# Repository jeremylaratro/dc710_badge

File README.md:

# DC710 Badge — DEF CON 34 (B-2 Spirit)

Flying-wing PCB badge in a real B-2 Spirit silhouette.  ESP32-C3 +
SA868-V VHF transceiver, single-cell LiPo, USB-C charging, OLED display,
4× WS2812 RGB LEDs, 3× tactile buttons, SAO header.

**Board:** 200 × 77 mm (≈ 7.87" tip-to-tip), real B-2 proportions
(wingspan/length ≈ 2.5).  Outline extracted from a real B-2 STL mesh —
3 aft-pointing spikes, engine-cutout notches, sharp swept wingtips.

### 3D render — Top (F.Cu)

### 3D render — Bottom (B.Cu)

### Official blueprint — Front

### Official blueprint — Back

---

## What's in the project

### Hardware
- **MCU:** ESP32-C3-MINI-1 module (official Espressif footprint, 53 pads)
- **Radio:** G-NiceRF SA868-V VHF (134–174 MHz) walkie-talkie module
- **Display:** SSD1306 0.96" OLED, 7-pin SPI
- **Power:** USB-C → SS14 Schottky → TP4056 LiPo charger → AP2112K-3.3 LDO
- **Battery:** Single-cell LiPo via JST-PH 2-pin
- **UI:** 4× WS2812B-2020 RGB LEDs, 3× TL3342 tactile (RESET / SEL / UP / DN), green status LED
- **Expansion:** SAO v1.69bis 2x3 header, 1×4 debug UART header

---

## ESP32-C3 GPIO map

| GPIO | Pad | Function |
|---|---|---|
| EN  |  6 | Reset (S1 + R4 + C7 RC) |
| 0   | 13 | WS2812 LED chain DIN (R11 220Ω series) |
| 1   | 14 | OLED DC |
| 2   |  7 | SA868 audio RX (ADC1_CH2, mid-rail biased) |
| 3   |  8 | UP button |
| 4   | 27 | SA868 PTT |
| 5   | 28 | OLED CS |
| 6   | 30 | OLED SCK |
| 7   | 31 | OLED MOSI |
| 8   | 20 | DOWN button (strap, pull-up at boot) |
| 9   | 19 | SEL / BOOT (strap, pull-up) |
| 10  | 11 | SA868 UART TX (UART1) |
| 18  | 16 | USB D− |
| 19  | 17 | USB D+ |
| 20  | 23 | SA868 UART RX |
| 21  | 24 | OLED RES |

---

## What's left to hand-finish

- [x] Route the 3 remaining nets in pcbnew (audio LPF cluster).
- [x] Move 4 short traces out of the antenna keep-out zones (RF perf).
- [x] Reposition silkscreen reference designators that overlap pads.
- [ ] Complete firmware development
- [ ] Complete hardware CTF
- [ ] Order Gerbers 

---

## Potential Obstacles

1. **PCB trace antenna performance at VHF will be poor.**  ~150 mm of
   meander on a flying-wing PCB at 145 MHz is electrically short — expect
   single-digit-negative dBi gain.  Fine for in-room foxhunt; not for DX.
   The match network has DNP shunts (C50 / C51) for VNA tuning.
2. **SA868 footprint is hand-built from the NiceRF datasheet.** 
3. **Audio TX synthesis uses `ledcWriteTone()`.**  Adequate for CW /
   beacon tones, not arbitrary audio.

---

## Previous edition

The DEF CON 33 design (smaller 100 × 55 mm board, 3-triangle outline,
hand-rolled symbols) lives in [`defcon33/`](defcon33/).

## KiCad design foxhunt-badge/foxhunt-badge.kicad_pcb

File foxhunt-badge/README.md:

# Foxhunt Badge — DEFCON B-2 Edition

ESP32-C3 + SA868-V VHF transceiver in a B-2 Spirit silhouette PCB.
~$16 BOM at qty 100, single-cell LiPo, **200×80mm** flying-wing form
factor (~7.87" tip-to-tip, real B-2 proportions: wingspan/length ≈ 2.5,
~31° leading-edge sweep).

> **Status (2026-04-25, v1.2): KiCad 9 schematic ERC-clean (0 errors,
> 0 warnings).  PCB on 200×80 mm B-2 outline (4 aft-pointing apexes + 3
> forward notches including center notch).  All 56 footprints inside the
> outline.  U2 uses the **official Espressif ESP32-C3-MINI-1 footprint**
> (53 pads, fetched from github.com/espressif/kicad-libraries).  The
> netlist pin numbers match the official datasheet pinout exactly.
> Freerouting v2.1.0 routed **119 of 131 nets (350 track segments)** in
> a 30-pass autoroute.  12 nets remain unrouted in the dense central
> module area; these need hand-finishing in pcbnew.**

---

## Project layout

```
foxhunt-badge/
├── foxhunt-badge.kicad_pro      # KiCad 9 project file
├── foxhunt-badge.kicad_sch      # schematic (ERC-clean)
├── foxhunt-badge.kicad_pcb      # PCB (placed, ground-poured, awaiting routing)
├── sym-lib-table                # registers project symbol library
├── fp-lib-table                 # registers project footprint library
├── lib/
│   ├── foxhunt.kicad_sym        # custom symbols (ESP32-C3-MINI-1, SA868,
│   │                            #                 TP4056_Module, OLED_SSD1306)
│   └── foxhunt.pretty/          # custom footprints
├── docs/                        # netlist + placement reference
├── fab/
│   ├── lib_gen.py               # regenerate lib/foxhunt.kicad_sym
│   ├── footprint_gen.py         # regenerate lib/foxhunt.pretty/
│   ├── sch_gen.py               # regenerate the schematic
│   ├── pcb_gen.py               # regenerate the PCB
│   ├── generate_b2_outline.py   # parametric B-2 outline generator
│   └── output/                  # Gerbers, drill, BOM, position files
└── firmware/                    # PlatformIO ESP-IDF firmware
```

## What's in the schematic (59 components, 43 nets)

* **Power tree:** USB-C 16P → SS14 Schottky → TP4056 LiPo charger → AP2112K-3.3
  LDO → 3.3 V rail.  3 PWR_FLAG drivers (VBUS, VBAT_RAW, GND) keep ERC happy.
* **MCU:** ESP32-C3-MINI-1 with EN reset RC, 10 µF / 1 µF / 100 nF decoupling,
  RESET / SEL / UP / DN tactiles, USB-C as native USB 2.0 (CDC) plus UART debug
  pass-through (J3).
* **Radio:** SA868-V (VHF) module with PTT / PD pull-ups, UART1 control, audio
  TX low-pass network (R-C-R-C-C), audio RX bias network (DC-block + mid-rail
  divider), trace-antenna match (L1 + DNP shunt caps for VNA tuning).
* **UI:** SSD1306 SPI 0.96" OLED, four WS2812B-2020 RGB LEDs in a chain along
  the leading edge, status LED, 2×3 SAO header, 1×4 debug header.

## ESP32-C3 pin map

| GPIO | Function          |
|------|-------------------|
| 0    | WS2812 DIN        |
| 1    | OLED_DC           |
| 2    | SA868_AUDIO (ADC) |
| 3    | BTN_UP            |
| 4    | SA868_PTT         |
| 5    | OLED_CS           |
| 6    | OLED_SCK          |
| 7    | OLED_MOSI         |
| 8    | BTN_DN            |
| 9    | BTN_SEL (boot)    |
| 10   | SA868_TX (UART1)  |
| 18   | USB_DM            |
| 19   | USB_DP            |
| 20   | SA868_RX (UART1)  |
| 21   | OLED_RST          |

## What still needs hand-finishing

The auto-generated PCB has all footprints positioned and nets assigned, but
the following still need attention in the KiCad GUI:

1. **Routing.** 132 ratsnest connections remain.  Suggested order:
   1. VBUS / VBAT / +3V3 power tree (use 0.5 mm tracks, Power netclass).
   2. RF chain U3.ANT → L1 → trace antenna (Right wingtip, RF netclass).
   3. Audio paths (MIC / RX_OUT) — keep away from WS2812 DIN.
   4. WS2812 daisy-chain along the leading edge.
   5. OLED SPI bus (group SCK/MOSI together).
   6. Buttons, debug header, SAO.
2. **Placement refinement.** ~10 components have minor courtyard overlaps
   from the auto-placer; spread them slightly in the GUI.
3. **Silkscreen.** Reference designators may need to be moved off pads
   (silk-on-copper warnings).
4. **Final DRC pass** before plotting fab outputs.

## Regenerating the project from scratch

```bash
# Library
python3 fab/lib_gen.py
python3 fab/footprint_gen.py

# Schematic + PCB
python3 fab/sch_gen.py
python3 fab/pcb_gen.py

# Validation
kicad-cli sch erc -o /tmp/erc.rpt foxhunt-badge.kicad_sch   # 0 violations
kicad-cli pcb drc -o /tmp/drc.rpt foxhunt-badge.kicad_pcb   # 132 unconnected (ratsnest)

# Fab outputs (after routing in GUI)
mkdir -p fab/output
kicad-cli pcb export gerbers --output fab/output/ foxhunt-badge.kicad_pcb
kicad-cli pcb export drill   --output fab/output/ foxhunt-badge.kicad_pcb
kicad-cli pcb export pos     --output fab/output/foxhunt-badge-pos.csv \
                             --format csv --units mm foxhunt-badge.kicad_pcb
kicad-cli sch export bom     --output fab/output/foxhunt-badge-bom.csv \
                             --fields "Reference,Value,Footprint,MPN,LCSC" \
                             --group-by Value foxhunt-badge.kicad_sch
```

## Custom libraries

Because KiCad's stock libraries don't ship the exact parts we use, four
custom symbols and four custom footprints live in `lib/`:

| Item                          | Symbol | Footprint | Source                             |
|-------------------------------|--------|-----------|------------------------------------|
| ESP32-C3-MINI-1 (53-pad MSMD) | ✓      | ✓         | Espressif datasheet rev 1.1        |
| SA868-V (16-pin castellated)  | ✓      | ✓         | NiceRF SA868 datasheet             |
| TP4056_Module (5-pin breakout)| ✓      | ✓         | LCSC C16581 module                 |
| OLED_SSD1306 7-pin SPI        | ✓      | ✓         | Generic 0.96" OLED breakout        |

These are registered via `sym-lib-table` and `fp-lib-table` and pinned in
the project preferences so they show up first in the picker.

## Firmware build & flash

```bash
cd firmware
pio run                  # build
pio run -t upload        # flash via USB-C
pio device monitor       # serial console at 115200
```

First boot: rainbow chase LEDs, splash OLED, idle animation.
SEL button cycles modes (IDLE → FOX → HUNTER → IDLE).

**Frequency configuration**: `main.cpp` defaults to 146.520 MHz (US 2m
simplex).  Transmitting on this freq requires a US Technician ham license.
For license-free testing, use a SA868-U (UHF) on PMR446 with a shorter
antenna meander.

## Honest disclosures

1. **PCB trace antenna performance at VHF will be poor.**  ~150 mm of meander
   on a 100 mm board at 145 MHz is electrically short — single-digit-negative
   dBi gain expected.  Fine for in-room foxhunt; not for DX.  The match
   network has DNP shunts (C50 / C51) for VNA tuning.  Next rev: add a u.FL
   footprint for an external whip.
2. **SA868 footprint is hand-built from the datasheet.**  Verify the pad
   geometry against your actual modules before fab.
3. **Audio TX synthesis uses ledcWriteTone().**  Adequate for CW/beacon tones,
   not arbitrary audio.  Voice TX would need an external I²S DAC.
4. **Routing is hand-finishing work.**  This generator places components and
   wires nets in the schematic; track routing is left to the GUI (or to a
   freerouting/specctra round-trip).  The placement plan in `docs/` is the
   intended ground truth for layout.

## Next-rev wishlist

* u.FL connector + external VHF whip
* PAM8302 + 8 Ω speaker for RX audio
* ESP32-S3 for more flash / GPIO / color OLED
* Full SAO v1.69bis compliance (needs 4 free GPIOs — likely requires an I/O
  expander on this rev's pin budget)

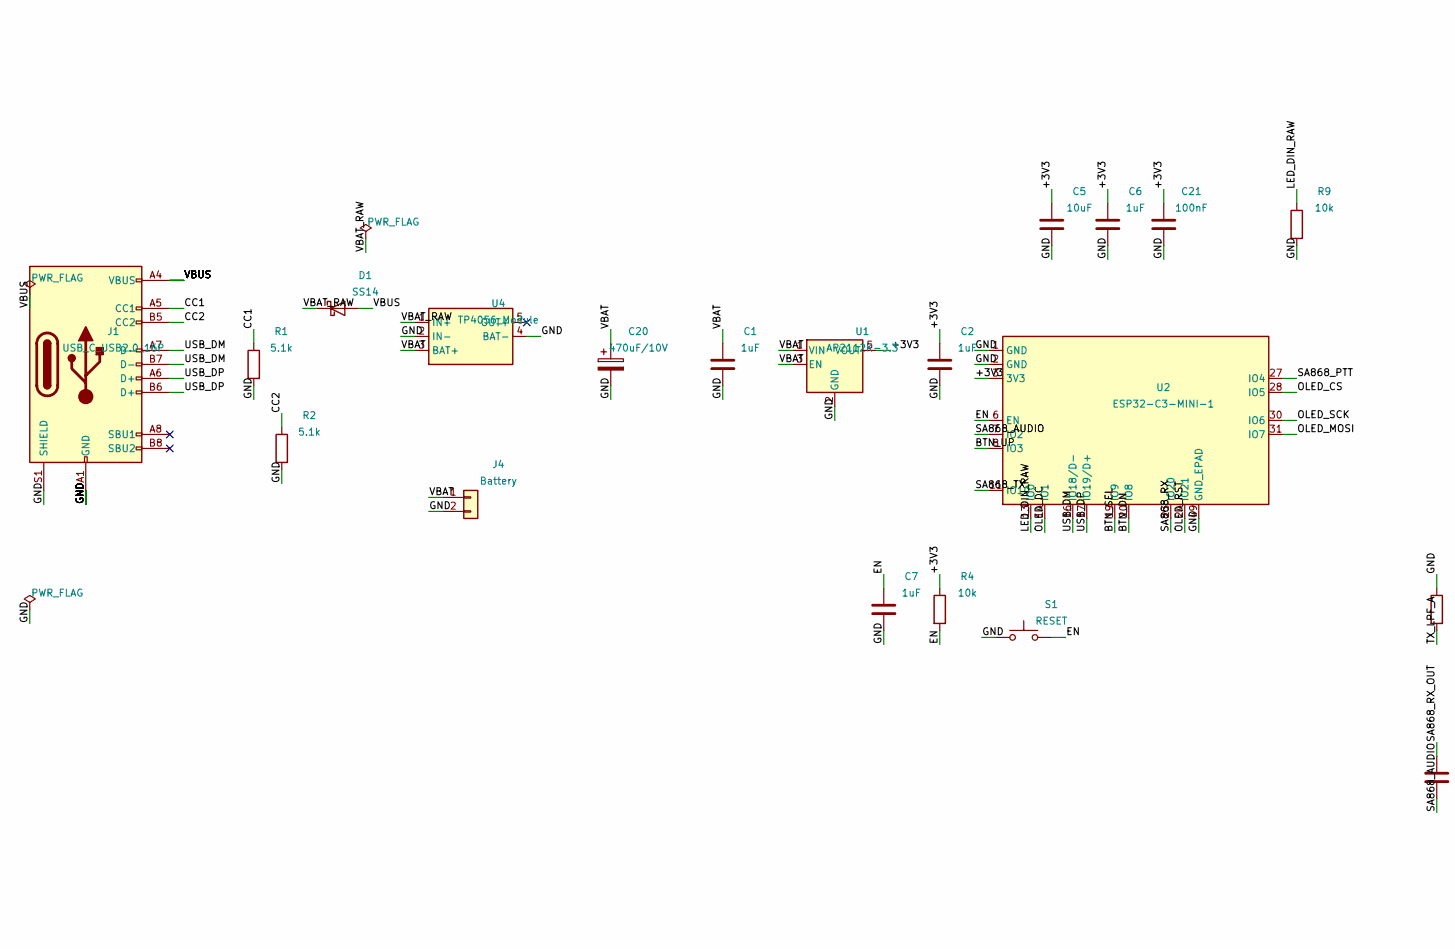
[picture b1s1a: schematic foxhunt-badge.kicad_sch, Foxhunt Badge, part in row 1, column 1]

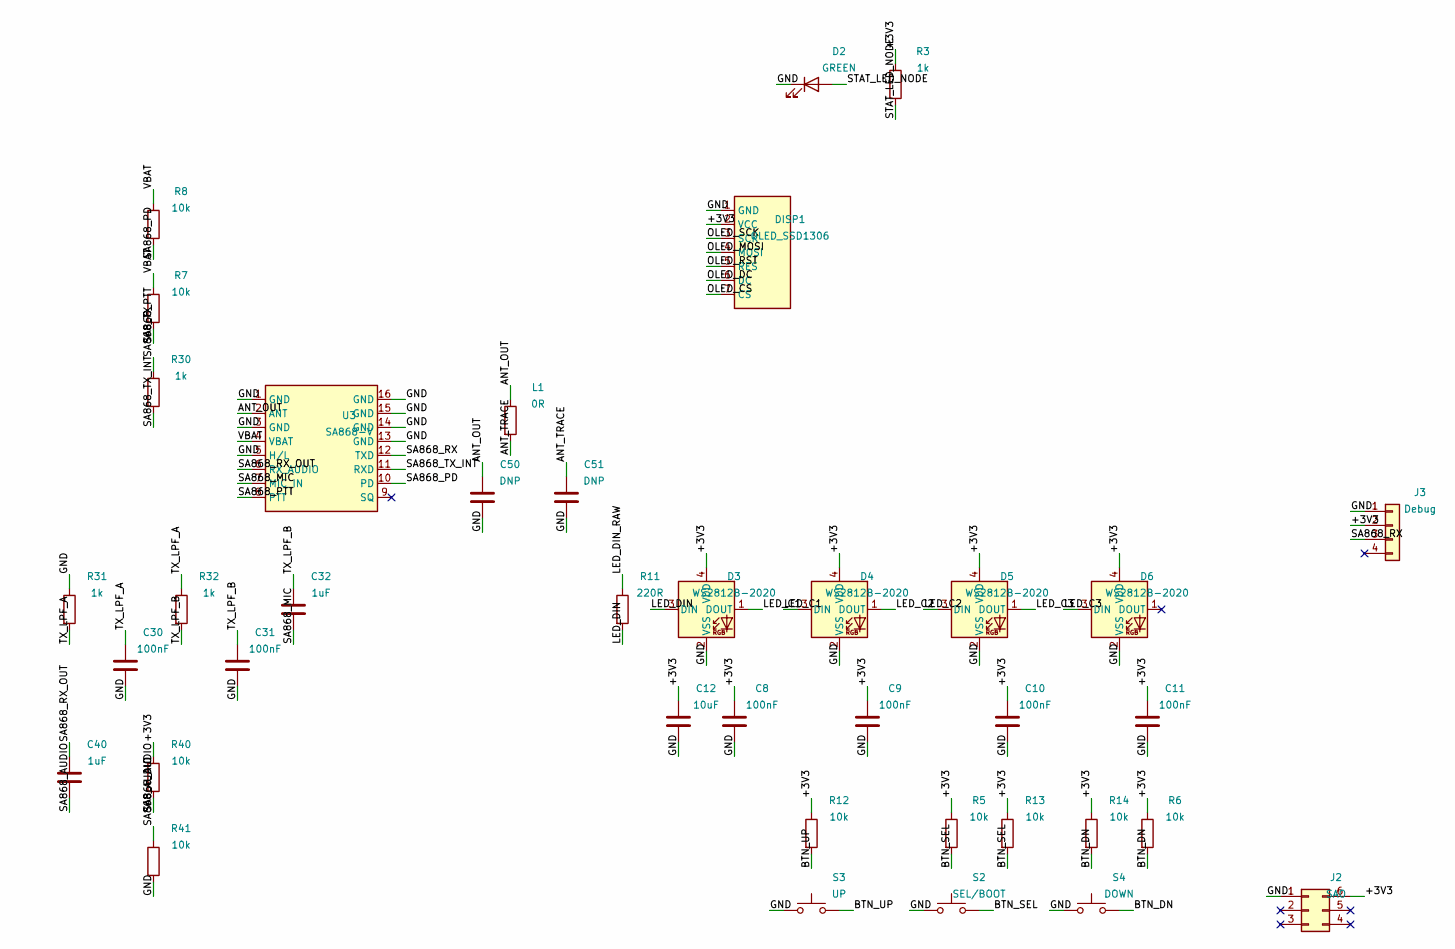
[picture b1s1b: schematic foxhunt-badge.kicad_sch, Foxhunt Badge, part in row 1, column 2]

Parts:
C1, C2, C6, C7, C32, C40: 1uF; C_0603_1608Metric
C5, C12: 10uF; C_0603_1608Metric
C8, C9, C10, C11, C21, C30, C31: 100nF; C_0603_1608Metric
C20: 470uF/10V; CP_Elec_8x10
C50, C51: DNP; C_0603_1608Metric
D1: SS14; D_SOD-123
D2: GREEN; LED_0603_1608Metric
D3, D4, D5, D6: WS2812B-2020; LED_WS2812B-2020_PLCC4_2.0x2.0mm
DISP1: OLED_SSD1306; OLED_SSD1306_128x64_7P
J1: USB_C_USB2.0_16P; USB_C_Receptacle_HRO_TYPE-C-31-M-12
J2: SAO; PinHeader_2x03_P2.54mm_Vertical
J3: Debug; PinHeader_1x04_P2.54mm_Vertical
J4: Battery; JST_PH_S2B-PH-K_1x02_P2.00mm_Horizontal
L1: 0R; R_0603_1608Metric
R1, R2: 5.1k; R_0603_1608Metric
R3, R30, R31, R32: 1k; R_0603_1608Metric
R4, R5, R6, R7, R8, R9, R12, R13, R14, R40, R41: 10k; R_0603_1608Metric
R11: 220R; R_0603_1608Metric
S1: RESET; SW_SPST_TL3342
S2: SEL/BOOT; SW_SPST_TL3342
S3: UP; SW_SPST_TL3342
S4: DOWN; SW_SPST_TL3342
U1: AP2112K-3.3; SOT-23-5
U2: ESP32-C3-MINI-1
U3: SA868-V; SA868
U4: TP4056_Module

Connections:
+3V3: C2.1, C5.1, C6.1, C8.1, C9.1, C10.1, C11.1, C12.1, C21.1, D3.4 (VDD), D4.4 (VDD), D5.4 (VDD), D6.4 (VDD), DISP1.2 (VCC), J2.6, J3.2, R3.1, R4.1, R5.1, R6.1, R12.1, R13.1, R14.1, R40.1, U1.5 (VOUT), U2.3 (3V3)
ANT_OUT: C50.1, L1.1, U3.2 (ANT)
ANT_TRACE: C51.1, L1.2
BTN_DN: R6.2, R14.2, S4.2, U2.20 (IO8)
BTN_SEL: R5.2, R13.2, S2.2, U2.19 (IO9)
BTN_UP: R12.2, S3.2, U2.8 (IO3)
CC1: J1.A5 (CC1), R1.1
CC2: J1.B5 (CC2), R2.1
EN: C7.1, R4.2, S1.2, U2.6 (EN)
GND: C1.2, C2.2, C5.2, C6.2, C7.2, C8.2, C9.2, C10.2, C11.2, C12.2, C20.2, C21.2, C30.2, C31.2, C50.2, C51.2, D2.1 (K), D3.2 (VSS), D4.2 (VSS), D5.2 (VSS), D6.2 (VSS), DISP1.1 (GND), J1.A1 (GND), J1.A12 (GND), J1.B1 (GND), J1.B12 (GND), J1.S1 (SHIELD), J2.1, J3.1, J3.4, J4.2, R1.2, R2.2, R9.2, R31.1, R41.2, S1.1, S2.1, S3.1, S4.1, U1.2 (GND), U2.1 (GND), U2.2 (GND), U2.49 (GND_EPAD), U3.1 (GND), U3.3 (GND), U3.5 (H/L), U3.13 (GND), U3.14 (GND), U3.15 (GND), U3.16 (GND), U4.2 (IN-), U4.4 (BAT-)
LED_C1: D3.1 (DOUT), D4.3 (DIN)
LED_C2: D4.1 (DOUT), D5.3 (DIN)
LED_C3: D5.1 (DOUT), D6.3 (DIN)
LED_DIN: D3.3 (DIN), R11.2
LED_DIN_RAW: R9.1, R11.1, U2.13 (IO0)
LED_END: D6.1 (DOUT)
OLED_CS: DISP1.7 (CS), U2.28 (IO5)
OLED_DC: DISP1.6 (DC), U2.14 (IO1)
OLED_MOSI: DISP1.4 (MOSI), U2.31 (IO7)
OLED_RST: DISP1.5 (RES), U2.24 (IO21)
OLED_SCK: DISP1.3 (SCK), U2.30 (IO6)
SA868_AUDIO: C40.2, R40.2, R41.1, U2.7 (IO2)
SA868_MIC: C32.2, U3.7 (MIC_IN)
SA868_PD: R8.2, U3.10 (PD)
SA868_PTT: R7.2, U2.27 (IO4), U3.8 (PTT)
SA868_RX: J3.3, U2.23 (IO20), U3.12 (TXD)
SA868_RX_OUT: C40.1, U3.6 (RX_AUDIO)
SA868_SQ: U3.9 (SQ)
SA868_TX: R30.1, U2.11 (IO10)
SA868_TX_INT: R30.2, U3.11 (RXD)
SAO_GPIO1: J2.3
SAO_GPIO2: J2.2
SAO_GPIO3: J2.5
SAO_GPIO4: J2.4
STAT_LED_NODE: D2.2 (A), R3.2
TX_LPF_A: C30.1, R31.2, R32.1
TX_LPF_B: C31.1, C32.1, R32.2
USB_DM: J1.A7 (D-), J1.B7 (D-), U2.16 (IO18/D-)
USB_DP: J1.A6 (D+), J1.B6 (D+), U2.17 (IO19/D+)
USB_OUT: U4.5 (OUT+)
VBAT: C1.1, C20.1, J4.1, R7.1, R8.1, U1.1 (VIN), U1.3 (EN), U3.4 (VBAT), U4.3 (BAT+)
VBAT_RAW: D1.1 (K), U4.1 (IN+)
VBUS: D1.2 (A), J1.A4 (VBUS), J1.A9 (VBUS), J1.B4 (VBUS), J1.B9 (VBUS)

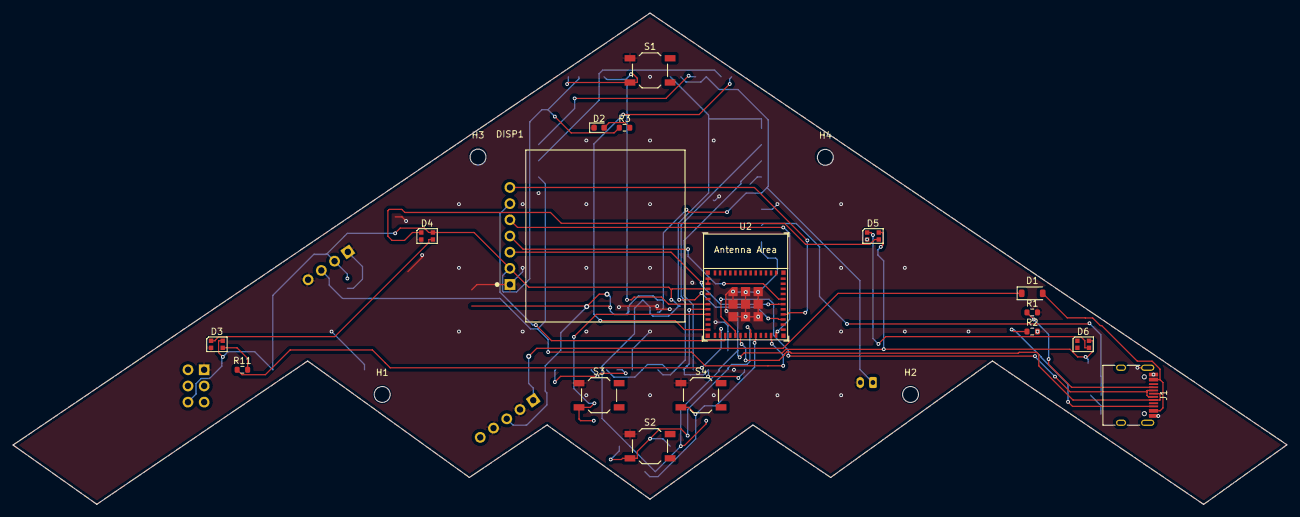
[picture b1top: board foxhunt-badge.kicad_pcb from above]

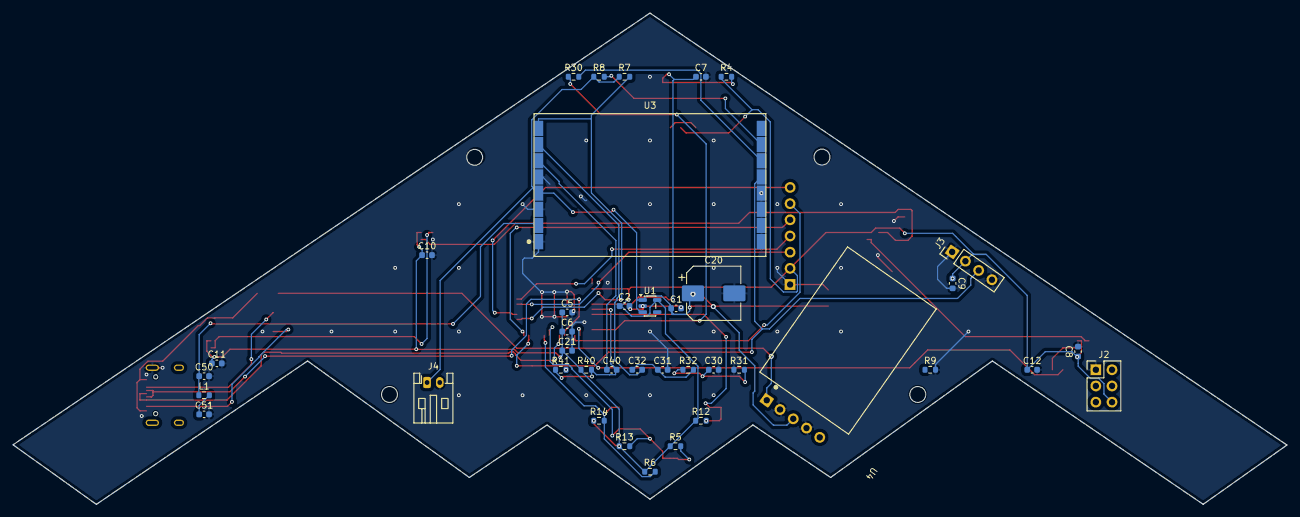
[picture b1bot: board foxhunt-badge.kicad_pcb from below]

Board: 2 copper layers, 200.0 x 77.1 mm, 60 parts (39 on the bottom side), 36 nets.

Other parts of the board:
H1, H2, H3, H4: MountingHole_2.5mm

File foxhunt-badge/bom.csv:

Reference,Qty,Value,Footprint,LCSC,Description
U1,1,AP2112K-3.3,SOT-23-5,C51118,3.3V LDO 600mA
U2,1,ESP32-C3-MINI-1,Module,C2934569,WiFi/BLE MCU module w/ integrated antenna
U3,1,SA868-V,Module,C5118772,VHF transceiver module 134-174MHz
U4,1,TP4056 module,Module-back,N/A,Pre-built 1S LiPo charger module (AliExpress/Amazon)
U5,1,USBLC6-2SC6,SOT-23-6,C7470,USB ESD protection (optional)
D1,1,SS14,SOD-123,C8678,Schottky diode reverse polarity
D2,1,LED-GREEN,0603,C72043,Power-on indicator
D3..D6,4,WS2812B-2020,WS2812-2020,C965555,RGB LED smart pixel
J1,1,USB-C 16P,USB-C-31-M-12,C165948,USB-C receptacle 16-pin
J2,1,SAO 2x3 Header,2.54mm 2x3,C124375,DEFCON SAO connector (1.69bis)
J3,1,Pin Header 1x4,2.54mm 1x4,C124375,Debug UART header
J4,1,JST PH 2P,PH-2A,C131350,LiPo battery connector
S1,1,Tactile SMD,4x4mm,C720477,RESET button
S2,1,Tactile SMD,4x4mm,C720477,BOOT/SEL button
S3,1,Tactile SMD,4x4mm,C720477,UP button
S4,1,Tactile SMD,4x4mm,C720477,DOWN button
DISP1,1,SSD1306 128x64 OLED,7-pin 0.96 module,C90364,SPI mono OLED module
BAT1,1,LiPo 500mAh,JST-PH 2-pin,N/A,1S LiPo 3.7V 500mAh (any cheap source)
ANT1,1,PCB trace,N/A,N/A,Meandered trace antenna right wingtip
R1,1,5.1k 0603,0603,C23186,USB-C CC1 pulldown
R2,1,5.1k 0603,0603,C23186,USB-C CC2 pulldown
R3,1,1k 0603,0603,C21190,Power LED current limit
R4,1,10k 0603,0603,C25804,EN pull-up
R5,1,10k 0603,0603,C25804,GPIO9 BOOT pull-up
R6,1,10k 0603,0603,C25804,GPIO8 OLED RST pull-up
R7,1,10k 0603,0603,C25804,SA868 PTT pull-up (idle RX)
R8,1,10k 0603,0603,C25804,SA868 PD pull-up
R9,1,10k 0603,0603,C25804,SA868 H/L tie high (1W TX)
R10,1,10k 0603,0603,C25804,GPIO2 strap pull-down
R11,1,220R 0603,0603,C22962,WS2812 first-LED data series resistor
R12..R14,3,10k 0603,0603,C25804,Button external pull-ups (UP/DN/SEL)
R30,1,1k 0603,0603,C21190,SA868 RXD series safety
R31,1,1k 0603,0603,C21190,Audio TX low-pass stage 1
R32,1,1k 0603,0603,C21190,Audio TX low-pass stage 2
R40,1,10k 0603,0603,C25804,RX audio bias divider top
R41,1,10k 0603,0603,C25804,RX audio bias divider bottom
C1,1,1uF 0603,0603,C15849,LDO Vin
C2,1,1uF 0603,0603,C15849,LDO Vout
C3,1,100nF 0603,0603,C14663,USB VBUS bypass
C4,1,10uF 0603,0603,C19702,+3V3 bulk
C5,1,100nF 0603,0603,C14663,ESP32 module +3V3 decouple
C6,1,10uF 0603,0603,C19702,ESP32 module +3V3 bulk
C7,1,1uF 0603,0603,C15849,EN reset cap
C8,1,100nF 0603,0603,C14663,WS2812 first decouple
C9,1,100nF 0603,0603,C14663,WS2812 #2 decouple
C10,1,100nF 0603,0603,C14663,WS2812 #3 decouple
C11,1,100nF 0603,0603,C14663,WS2812 #4 decouple
C12,1,10uF 0603,0603,C19702,WS2812 chain bulk
C20,1,470uF 6.3V,SMD radial 8x10,C16133,SA868 VBAT bulk (LOW ESR)
C21,1,100nF 0603,0603,C14663,SA868 VBAT HF decouple (next to pin 4)
C30,1,100nF 0603,0603,C14663,Audio LPF stage 1
C31,1,100nF 0603,0603,C14663,Audio LPF stage 2
C32,1,1uF 0603,0603,C15849,Audio TX DC block
C40,1,1uF 0603,0603,C15849,Audio RX DC block
L1,1,0R jumper 0603,0603,C17168,RF match L slot (start with 0R)
C50,1,DNP,0603,N/A,RF match shunt 1 (populate after VNA tuning)
C51,1,DNP,0603,N/A,RF match shunt 2 (populate after VNA tuning)

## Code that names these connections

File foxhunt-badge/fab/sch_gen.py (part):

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    "CC1": [("J1", "A5"), ("R1", "1")],
    "CC2": [("J1", "B5"), ("R2", "1")],
    # ---- USB D+/D- ----
    "USB_DP": [("J1", "A6"), ("J1", "B6"), ("U2", "17")],   # GPIO19 = pad 17
    "USB_DM": [("J1", "A7"), ("J1", "B7"), ("U2", "16")],   # GPIO18 = pad 16
    # ---- EN reset RC ----
    "EN": [("U2", "6"), ("R4", "2"), ("S1", "2"), ("C7", "1")],   # CHIP_PU = pad 6
    # ---- Status LED chain ----
    "STAT_LED_NODE": [("R3", "2"), ("D2", "2")],
    # ---- WS2812 chain (GPIO0 -> R11 220R -> D3..D6) ----
    "LED_DIN_RAW": [("U2", "13"), ("R11", "1"), ("R9", "1")], # GPIO0 = pad 13
    "LED_DIN":     [("R11", "2"), ("D3", "3")],
    "LED_C1":      [("D3", "1"), ("D4", "3")],
    "LED_C2":      [("D4", "1"), ("D5", "3")],
    "LED_C3":      [("D5", "1"), ("D6", "3")],
    "LED_END":     [("D6", "1")],
    # ---- OLED SPI ----
    "OLED_CS":   [("U2", "28"), ("DISP1", "7")],   # GPIO5 = pad 28
    "OLED_SCK":  [("U2", "30"), ("DISP1", "3")],   # GPIO6 = pad 30
    "OLED_MOSI": [("U2", "31"), ("DISP1", "4")],   # GPIO7 = pad 31
    "OLED_DC":   [("U2", "14"), ("DISP1", "6")],   # GPIO1 = pad 14
    "OLED_RST":  [("U2", "24"), ("DISP1", "5")],   # GPIO21 = pad 24
    # ---- SA868 control ----
    "SA868_PTT": [("U2", "27"), ("U3", "8"),  ("R7", "2")],   # GPIO4 = pad 27
    "SA868_PD":  [("U3", "10"), ("R8", "2")],                  # PD held high via R8
    "SA868_TX":  [("U2", "11"), ("R30", "1")],                 # GPIO10 = pad 11
    "SA868_RX":  [("U2", "23"), ("U3", "12"), ("J3", "3")],   # GPIO20 = pad 23; debug tap
    "SA868_TX_INT": [("R30", "2"), ("U3", "11")],              # series resistor to RXD
    "SA868_SQ":  [("U3", "9")],                                # squelch — leave as NC
    # ---- Audio TX path (GPIO not assigned in this rev — direct GPIO would
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    "ANT_OUT":   [("U3", "2"), ("L1", "1"), ("C50", "1")],
    "ANT_TRACE": [("L1", "2"), ("C51", "1")],
    # ---- Buttons ----
    "BTN_UP":    [("U2", "8"),  ("S3", "2"), ("R12", "2")],   # GPIO3 = pad 8
    "BTN_SEL":   [("U2", "19"), ("S2", "2"), ("R5", "2"),
                  ("R13", "2")],                                # GPIO9 = pad 19
    "BTN_DN":    [("U2", "20"), ("S4", "2"), ("R14", "2"),
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
# Power nets that should use power symbols instead of net labels at every
# pin (KiCad convention).  Stock power lib has GND, +3V3, VBUS but no
# VBAT; VBAT/VBAT_RAW remain as net labels.
POWER_SYMBOL_NET = {
    "GND":      "power:GND",
    "+3V3":     "power:+3V3",
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
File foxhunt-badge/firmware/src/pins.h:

// pins.h -- Foxhunt Badge ESP32-C3 pin map
// Single source of truth. Change here, propagate everywhere.
#pragma once

#include <Arduino.h>

// ---- LED chain ----
constexpr uint8_t PIN_LED_DIN   = 0;
constexpr uint8_t NUM_LEDS      = 4;

// ---- OLED (SPI) ----
constexpr uint8_t PIN_OLED_DC   = 1;
constexpr uint8_t PIN_OLED_CS   = 5;
constexpr uint8_t PIN_OLED_SCK  = 6;
constexpr uint8_t PIN_OLED_MOSI = 7;
constexpr uint8_t PIN_OLED_RST  = 8;

// ---- Buttons (active low, internal pullups OK on non-strap pins) ----
constexpr uint8_t PIN_BTN_UP    = 3;
constexpr uint8_t PIN_BTN_SEL   = 9;   // doubles as BOOT
constexpr uint8_t PIN_BTN_DN    = 17;

// ---- SA868 radio ----
constexpr uint8_t PIN_SA868_PTT      = 10;  // active low
constexpr uint8_t PIN_SA868_UART_RX  = 11;  // ESP RX <- module TX
constexpr uint8_t PIN_SA868_UART_TX  = 12;  // ESP TX -> module RX
constexpr uint8_t PIN_SA868_PD       = 13;  // active low (low = sleep)
constexpr uint8_t PIN_SA868_MIC_PWM  = 15;  // PWM -> RC LPF -> MIC_IN
constexpr uint8_t PIN_SA868_RX_AUDIO = 16;  // ADC <- RX_OUT (AC-coupled)

// ---- Debug UART ----
constexpr uint8_t PIN_DBG_RX = 20;
constexpr uint8_t PIN_DBG_TX = 21;

// ---- Other ----
constexpr uint32_t MIC_PWM_FREQ_HZ   = 80000;   // out of audio band
constexpr uint8_t  MIC_PWM_RES_BITS  = 8;
constexpr uint8_t  MIC_PWM_CHANNEL   = 0;

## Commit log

2026-03-29 Add song playback assessment and implementation for ESP32 badge
    Demonstrates how to use ESP32 LEDC PWM to drive a piezo buzzer with
    musical note frequencies. Includes note definitions (C3-B7), a Note
    struct for song data, and four example songs.
    https://claude.ai/code/session_01RsCHAc1jCegj4mveaVEJUA
2026-04-26 DC710 badge — DEF CON 34 (B-2 Spirit)
    - 200x77mm B-2 silhouette PCB extracted from STL mesh (3 aft spikes,
    engine cutouts, swept leading edges) — real B-2 proportions.
    - ESP32-C3-MINI-1 + SA868-V VHF + SSD1306 OLED + 4x WS2812 + LiPo.
    - Schematic ERC-clean (0 errors / 0 warnings).
    - Freerouting v2.1.0 routed 128 of 131 nets (577 tracks + 63 GND vias).
    - Reproducible Python generators (lib_gen, footprint_gen, sch_gen,
2026-04-26 Update README with completed tasks
2026-04-26 README: cropped board renders + official blueprint views
    - images/badge_top.png and images/badge_bottom.png: user-cropped 3D renders
    - images/badge_front_blueprint.png and images/badge_back_blueprint.png:
    official KiCad-plotted PCB blueprints (rev 0.6) converted from PDF
2026-04-26 Schematic: use stock power symbols (GND/+3V3/VBUS) for power nets
